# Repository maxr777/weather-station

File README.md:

# Weather Station
ESP32-based weather station built with ESP-IDF, no third-party sensor libraries. A handmade rewrite of an earlier Arduino IDE version that relied on libraries. Also taken further: soldered onto a perfboard with a 3D printed enclosure instead of a breadboard.

Reads temperature, humidity, and pressure via a BME280 over I2C, monitors air quality with a PMS5003 over UART, and displays everything on an SH1106 OLED. A few diagnostic LEDs signal hardware faults on startup.

All sensor drivers written from scratch against the datasheets. Structured as pure header-only libraries — an experiment after building projects with both the classic .h/.c split and unity builds. Uses Raylib naming conventions - I'd use [Tiger Style](https://tigerstyle.dev/#nouns-and-verbs) if starting it today. Font by [petabyt](https://github.com/petabyt/font). Startup logo generated with Claude.

## Demo

*Low res thumbnails — click to watch on YouTube*

## Schematic

## Build
`idf.py build flash monitor` (run from the root directory, not `main/`)

## Notes
- Enum names ended up too verbose - need to be more conservative with it
- Tiger Style's big-endian naming is so much better (`BME280_setup()` over `setup_BME280()`) - it reads better and works great with autocomplete
- camelCase is harder to read and is a headache sometimes (e.g. `0` followed by `O`, or `GetLEDGPIO`) - definitely use snake_case

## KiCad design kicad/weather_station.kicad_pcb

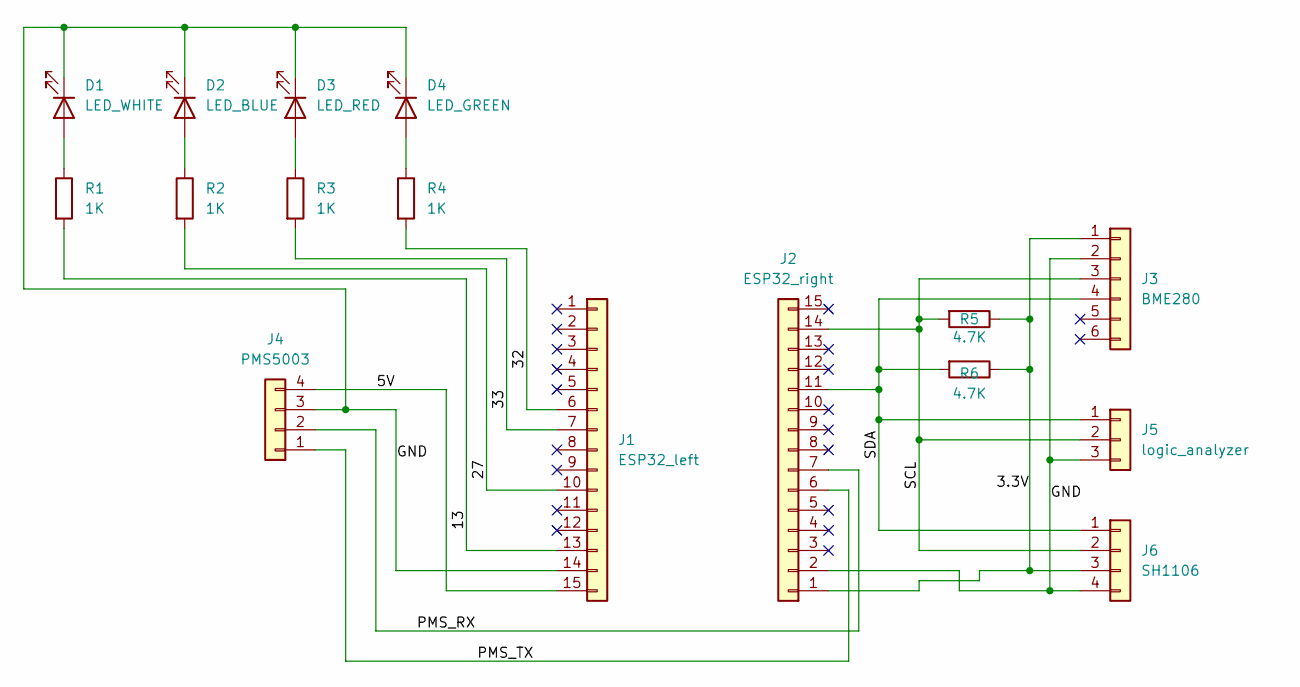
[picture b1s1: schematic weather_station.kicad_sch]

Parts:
D1: LED_WHITE; LED_0805_2012Metric
D2: LED_BLUE; LED_0805_2012Metric
D3: LED_RED; LED_0805_2012Metric
D4: LED_GREEN; LED_0805_2012Metric
J1: ESP32_left; PinHeader_1x15_P2.54mm_Vertical
J2: ESP32_right; PinHeader_1x15_P2.54mm_Vertical
J3: BME280; PinHeader_1x06_P2.54mm_Vertical
J4: PMS5003; PinHeader_1x04_P2.54mm_Vertical
J5: logic_analyzer; PinHeader_1x03_P2.54mm_Vertical
J6: SH1106; PinHeader_1x04_P2.54mm_Vertical
R1, R2, R3, R4: 1K; R_0805_2012Metric
R5, R6: 4.7K; R_0805_2012Metric

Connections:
/3.3V: J2.1, J3.1, J6.3, R5.1, R6.1
/5V: J1.15, J4.4
/13: J1.13, R1.2
/27: J1.10, R2.2
/32: J1.6, R4.2
/33: J1.7, R3.2
/GND: D1.1 (K), D2.1 (K), D3.1 (K), D4.1 (K), J1.14, J2.2, J3.2, J4.3, J5.3, J6.4
/PMS_RX: J2.7, J4.2
/PMS_TX: J2.6, J4.1
/SCL: J2.14, J3.3, J5.2, J6.2, R5.2
/SDA: J2.11, J3.4, J5.1, J6.1, R6.2
unnamed: D1.2 (A), R1.1
unnamed: D2.2 (A), R2.1
unnamed: D3.2 (A), R3.1
unnamed: D4.2 (A), R4.1

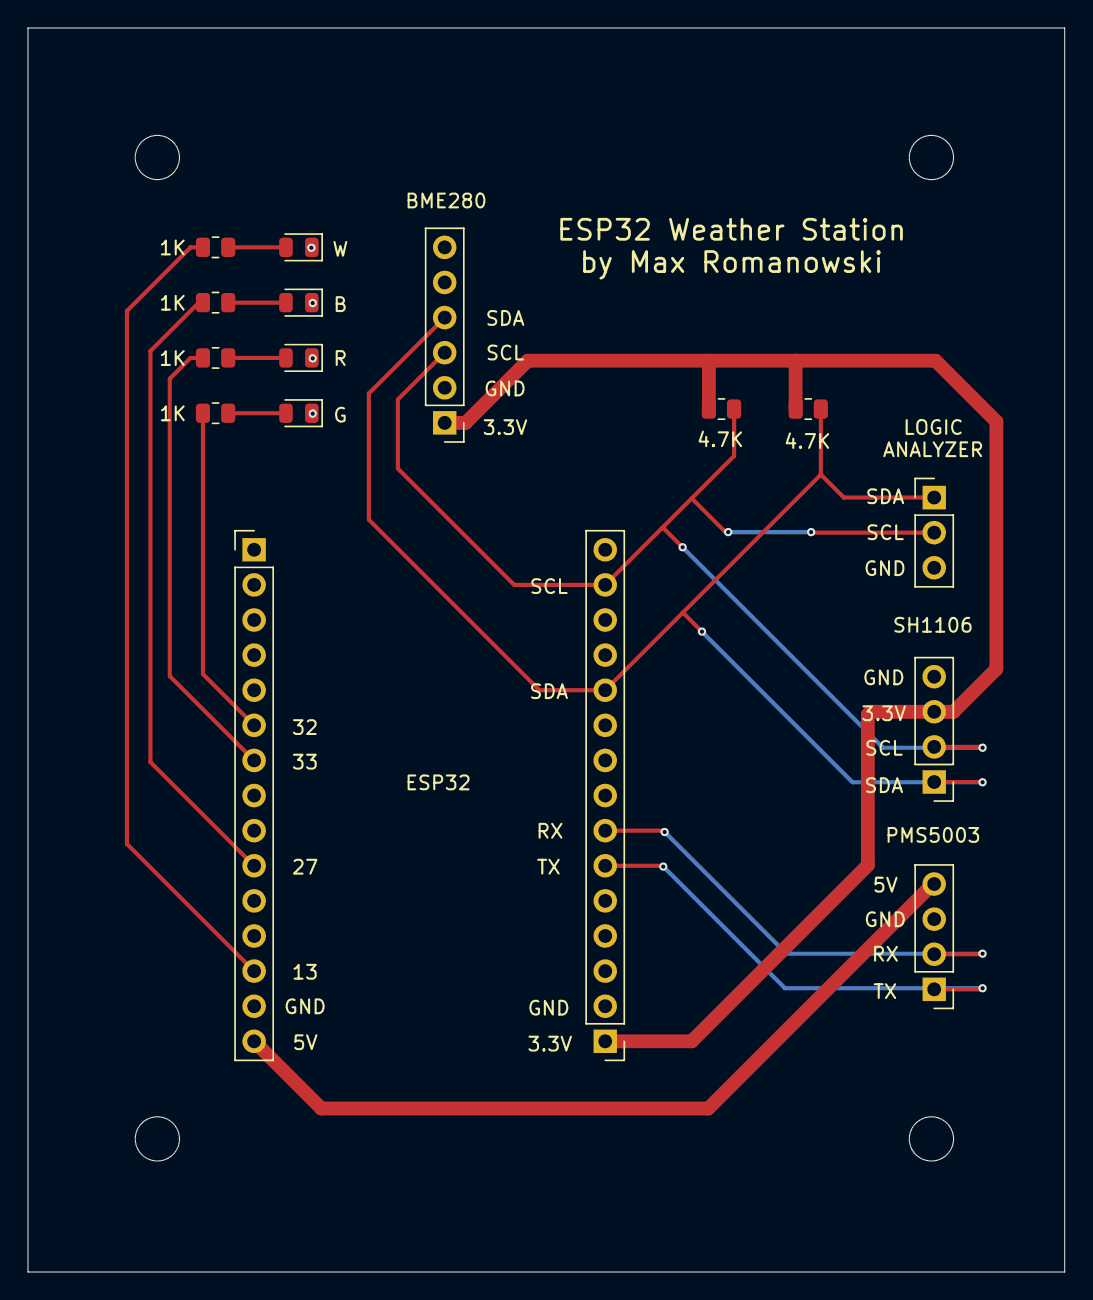
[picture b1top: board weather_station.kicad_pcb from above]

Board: 2 copper layers, 75.0 x 90.0 mm, 20 parts (0 on the bottom side), 15 nets.

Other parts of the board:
H1, H2, H3, H4: MountingHole_3.2mm_M3

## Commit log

2026-04-14 Get status lights to work
2026-04-15 Finish the bme280 setup
2026-04-16 tidy up
2026-04-16 bme280 done
2026-04-19 PMS5003 now works
2026-04-19 fixes
2026-04-25 Can draw with SH1106. Need to tweak the MS for i2c writes in the SH1106Flush() function - for some reason even with pullup resistors, 100ms is still timing out
2026-04-25 Forgot to commit, it mostly works now
2026-04-25 Indicate bad/old values, log reading errors
2026-04-25 Error check for calloc
2026-04-25 Finished?
2026-04-25 Clean up sdkconfig tracking and rename main source
2026-04-25 Remove old comment
2026-04-26 Add schematic
2026-04-26 Update README.md
    Added a demo section with a YouTube link and thumbnail.
2026-04-26 Fix schematic
2026-04-26 Fix schematic 2
2026-04-26 Fix schematic 3...
2026-04-26 Fix schematic 4
2026-05-05 The BME280 can now be hotswapped
2026-05-05 Small improvements to the setup code and PMS' data reading
2026-05-06 Add AIQ tiers (good, unhealthy, etc.) and remove the pms wait time in the setup
2026-05-08 Change wait time for pms reads, as it was sometimes getting stale reads
2026-05-08 Add kicad files
2026-05-14 Add SH1106 LED enable on error
